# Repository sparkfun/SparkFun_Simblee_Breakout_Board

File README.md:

**NOTE:** *This product has been retired from our catalog. If you are looking for more up-to-date info, please check out some of these resources to see how other users are still hacking and improving on this product.*
* *[SparkFun Forum](https://forum.sparkfun.com/)*
* *[Comments Here on GitHub](https://github.com/sparkfun/SparkFun_Simblee_Breakout_Board/issues)*
* *[IRC Channel](https://www.sparkfun.com/news/263)*

SparkFun Simblee Breakout Board
==================

The [SparkFun Simblee Breakout Board](https://www.sparkfun.com/products/13632) is a programmable board that allows you to add mobile app functionality via Bluetooth Low Energy (BLE, or Bluetooth 4.0) to your embedded projects. Unlike other BLE solutions, the Simblee requires no specialized app development skills to realize the phone-side interface; all the necessary coding is done in the Arduino environment and then uploaded to a browser app on the phone.

[  
*SparkFun Simblee Breakout Board*](https://www.sparkfun.com/products/13632)

Design files and firmware files for the [SparkFun Simblee Breakout Board](https://www.sparkfun.com/products/13632).

Repository Contents
-------------------

* **/hardware** - Eagle PCB layout files
* **/Production** - Files to support SparkFun production

Documentation
--------------
* **[Simblee Concepts](https://learn.sparkfun.com/tutorials/simblee-concepts)** - Information about Simblee
* **[Hookup Guide](https://learn.sparkfun.com/tutorials/simblee-breakout-board-hookup-guide)** - Basic hookup guide

License Information
-------------------

All contents of this repository are released under [Creative Commons Share-alike 4.0](http://creativecommons.org/licenses/by-sa/4.0/).

Authors: Mike Hord @ SparkFun Electonics

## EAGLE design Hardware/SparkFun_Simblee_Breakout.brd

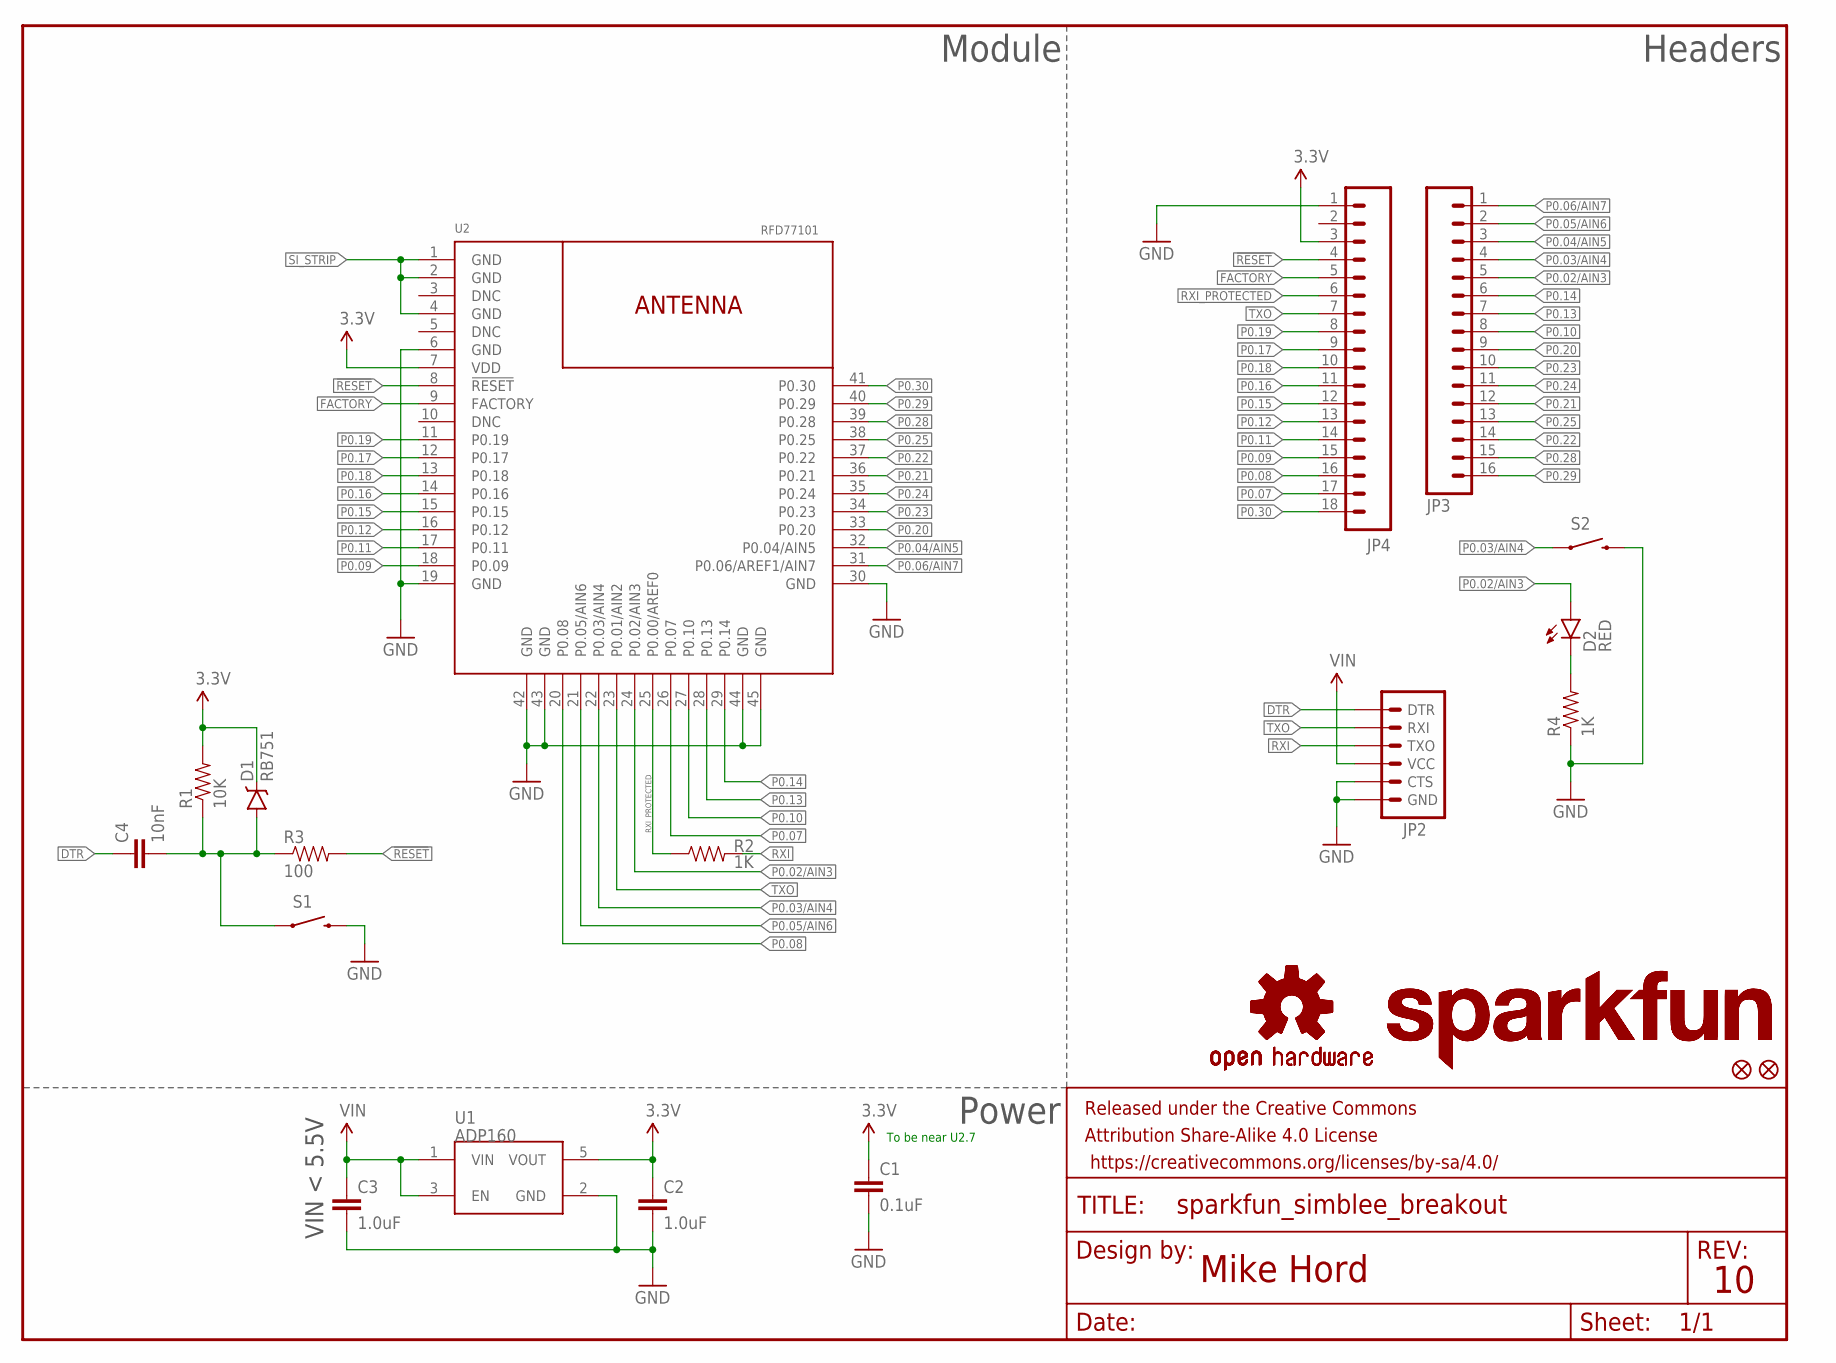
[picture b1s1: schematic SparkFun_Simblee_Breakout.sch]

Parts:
C1: 0.1uF; 0603-CAP
C2, C3: 1.0uF; 0603-CAP
C4: 10nF; 0603-CAP
D1: RB751; SOD-523
D2: RED; LED-0603
FID1, FID2: FIDUCIALUFIDUCIAL; MICRO-FIDUCIAL
FRAME1: FRAME-LETTER; CREATIVE_COMMONS
JP2: ARDUINO_SERIAL_PROGRAMPTH; 1X06
JP3: M16PTH; 1X16
JP4: M18_; 1X18
LOGO1, LOGO3: SFE_LOGO_NAME.1_INCH; SFE_LOGO_NAME_.1
LOGO2, LOGO4: OSHW-LOGOS; OSHW-LOGO-S
R1: 10K; 0603-RES
R2, R4: 1K; 0603-RES
R3: 100; 0603-RES
S1, S2: SWITCH-MOMENTARY-2SMD; TACTILE-SWITCH-SMD
U1: ADP160; SOT23-5
U2: RFD77101

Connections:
3.3V: C1.1, C2.1, D1.C, JP4.3, R1.2, U1.5 (VOUT), U2.7 (VDD)
!RESET: JP4.4, R3.2, U2.8 (!RESET!)
DTR: C4.1, JP2.1 (DTR)
FACTORY: JP4.5, U2.9 (FACTORY)
GND: C1.2, C2.2, C3.2, JP2.5 (CTS), JP2.6 (GND), JP4.1, R4.1, S1.3 (2), S2.3 (2), U1.2 (GND), U2.6 (GND), U2.19 (GND), U2.30 (GND), U2.42 (GND), U2.43 (GND), U2.44 (GND), U2.45 (GND)
unnamed: C4.2, D1.A, R1.1, R3.1, S1.1
unnamed: D2.C, R4.2
P0.02/AIN3: D2.A, JP3.5, U2.24 (P0.02/AIN3)
P0.03/AIN4: JP3.4, S2.1, U2.22 (P0.03/AIN4)
P0.04/AIN5: JP3.3, U2.32 (P0.04/AIN5)
P0.05/AIN6: JP3.2, U2.21 (P0.05/AIN6)
P0.06/AIN7: JP3.1, U2.31 (P0.06/AREF1/AIN7)
P0.07: JP4.17, U2.26 (P0.07)
P0.08: JP4.16, U2.20 (P0.08)
P0.09: JP4.15, U2.18 (P0.09)
P0.10: JP3.8, U2.27 (P0.10)
P0.11: JP4.14, U2.17 (P0.11)
P0.12: JP4.13, U2.16 (P0.12)
P0.13: JP3.7, U2.28 (P0.13)
P0.14: JP3.6, U2.29 (P0.14)
P0.15: JP4.12, U2.15 (P0.15)
P0.16: JP4.11, U2.14 (P0.16)
P0.17: JP4.9, U2.12 (P0.17)
P0.18: JP4.10, U2.13 (P0.18)
P0.19: JP4.8, U2.11 (P0.19)
P0.20: JP3.9, U2.33 (P0.20)
P0.21: JP3.12, U2.36 (P0.21)
P0.22: JP3.14, U2.37 (P0.22)
P0.23: JP3.10, U2.34 (P0.23)
P0.24: JP3.11, U2.35 (P0.24)
P0.25: JP3.13, U2.38 (P0.25)
P0.28: JP3.15, U2.39 (P0.28)
P0.29: JP3.16, U2.40 (P0.29)
P0.30: JP4.18, U2.41 (P0.30)
RXI: JP2.3 (TXO), R2.2
RXI_PROTECTED: JP4.6, R2.1, U2.25 (P0.00/AREF0)
SI_STRIP: U2.1 (GND), U2.2 (GND), U2.4 (GND)
TXO: JP2.2 (RXI), JP4.7, U2.23 (P0.01/AIN2)
VIN: C3.1, JP2.4 (VCC), U1.1 (VIN), U1.3 (EN)

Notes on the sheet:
Mike Hord
VIN < 5.5V
Module
Power
Headers
To be near U2.7

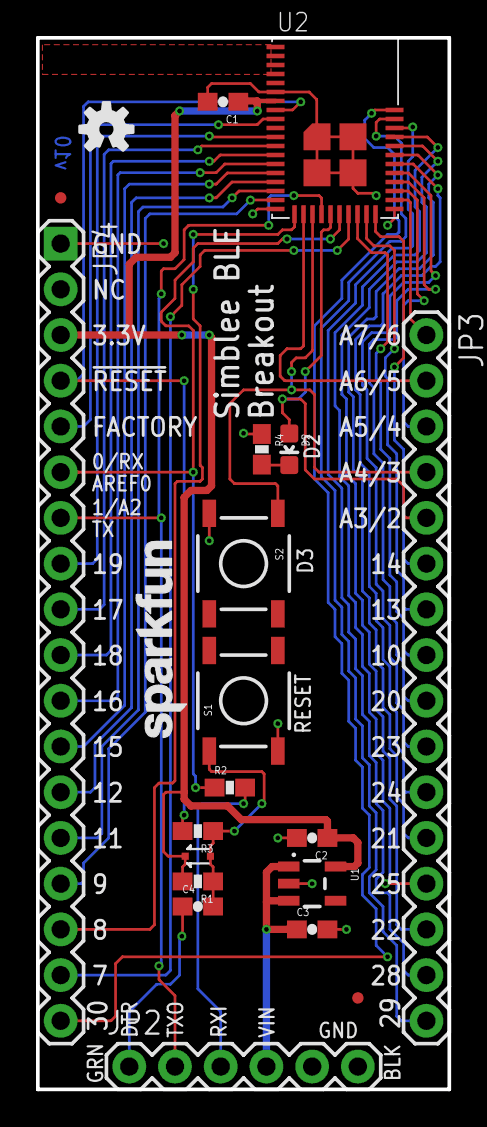
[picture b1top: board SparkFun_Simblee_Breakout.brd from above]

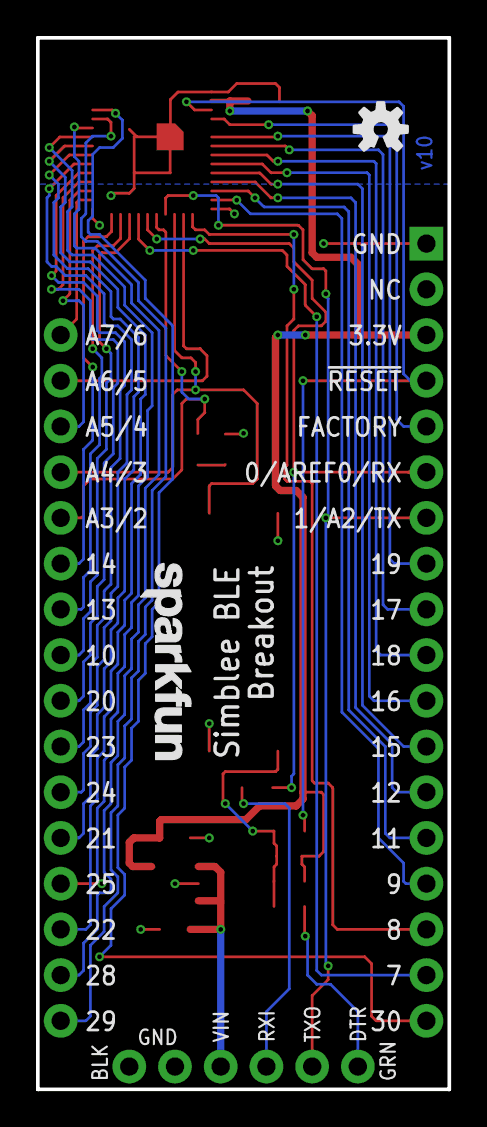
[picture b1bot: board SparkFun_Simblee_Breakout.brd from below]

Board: 2 copper layers, 22.9 x 58.4 mm, 24 parts (2 on the bottom side), 39 nets.

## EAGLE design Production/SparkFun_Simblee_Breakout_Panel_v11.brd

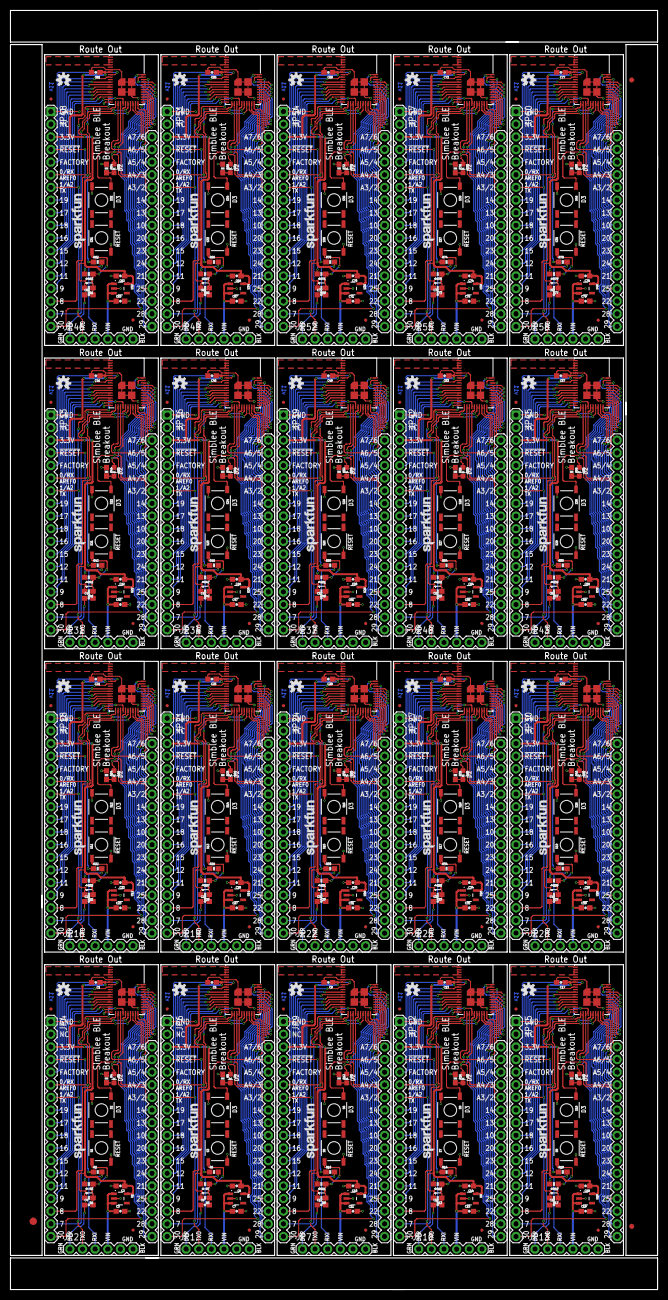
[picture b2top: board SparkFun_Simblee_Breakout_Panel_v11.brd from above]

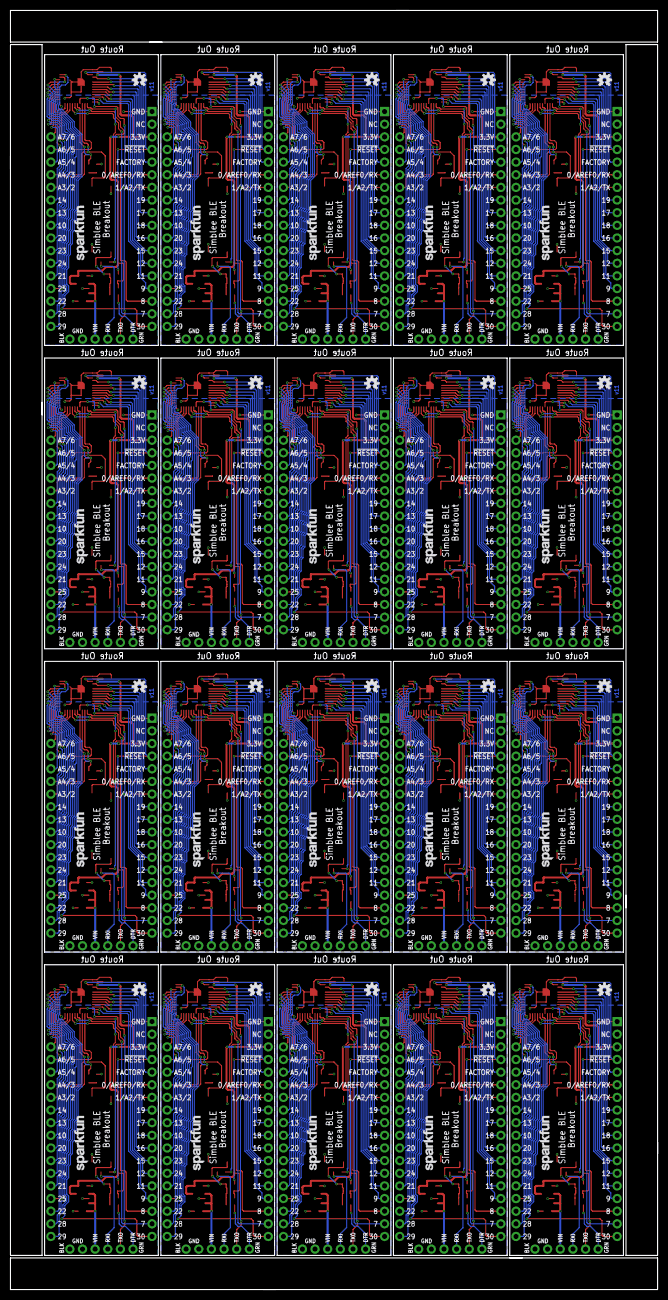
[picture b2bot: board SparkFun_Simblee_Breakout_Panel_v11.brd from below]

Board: 2 copper layers, 130.0 x 257.0 mm, 463 parts (40 on the bottom side), 780 nets.

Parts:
C1, C5, C9, C13, C17, C21, C25, C29, C33, C37, C41, C45, C49, C53, C57, C61, C65, C69, C73, C77: 0.1uF; 0603-CAP
C2, C3, C6, C7, C10, C11, C14, C15, C18, C19, C22, C23, C26, C27, C30, C31, C34, C35, C38, C39, C42, C43, C46, C47, C50, C51, C54, C55, C58, C59, C62, C63, C66, C67, C70, C71, C74, C75, C78, C79: 1.0uF; 0603-CAP
C4, C8, C12, C16, C20, C24, C28, C32, C36, C40, C44, C48, C52, C56, C60, C64, C68, C72, C76, C80: 10nF; 0603-CAP
D1, D3, D5, D7, D9, D11, D13, D15, D17, D19, D21, D23, D25, D27, D29, D31, D33, D35, D37, D39: RB751; SOD-523
D2, D4, D6, D8, D10, D12, D14, D16, D18, D20, D22, D24, D26, D28, D30, D32, D34, D36, D38, D40: RED; LED-0603
E$1: FIDUCIAL-1.5X3
E$5, E$6: FIDUCIAL-1X2
FID1, FID2, FID3, FID4, FID5, FID6, FID7, FID8, FID9, FID10, FID11, FID12, FID13, FID14, FID15, FID16, FID17, FID18, FID19, FID20, FID21, FID22, FID23, FID24, FID25, FID26, FID27, FID28, FID29, FID30, FID31, FID32, FID33, FID34, FID35, FID36, FID37, FID38, FID39, FID40: FIDUCIALUFIDUCIAL; MICRO-FIDUCIAL
JP1, JP2, JP7, JP10, JP13, JP16, JP19, JP22, JP25, JP28, JP31, JP34, JP37, JP40, JP43, JP46, JP49, JP52, JP55, JP58: 1X06
JP3, JP5, JP8, JP11, JP14, JP17, JP20, JP23, JP26, JP29, JP32, JP35, JP38, JP41, JP44, JP47, JP50, JP53, JP56, JP59: 1X16
JP4, JP6, JP9, JP12, JP15, JP18, JP21, JP24, JP27, JP30, JP33, JP36, JP39, JP42, JP45, JP48, JP51, JP54, JP57, JP60: 1X18
LOGO1, LOGO3, LOGO5, LOGO7, LOGO9, LOGO11, LOGO13, LOGO15, LOGO17, LOGO19, LOGO21, LOGO23, LOGO25, LOGO27, LOGO29, LOGO31, LOGO33, LOGO35, LOGO37, LOGO39, LOGO41, LOGO43, LOGO45, LOGO47, LOGO49, LOGO51, LOGO53, LOGO55, LOGO57, LOGO59, LOGO61, LOGO63, LOGO65, LOGO67, LOGO69, LOGO71, LOGO73, LOGO75, LOGO77, LOGO79: SFE_LOGO_NAME.1_INCH; SFE_LOGO_NAME_.1
LOGO2, LOGO4, LOGO6, LOGO8, LOGO10, LOGO12, LOGO14, LOGO16, LOGO18, LOGO20, LOGO22, LOGO24, LOGO26, LOGO28, LOGO30, LOGO32, LOGO34, LOGO36, LOGO38, LOGO40, LOGO42, LOGO44, LOGO46, LOGO48, LOGO50, LOGO52, LOGO54, LOGO56, LOGO58, LOGO60, LOGO62, LOGO64, LOGO66, LOGO68, LOGO70, LOGO72, LOGO74, LOGO76, LOGO78, LOGO80: OSHW-LOGOS; OSHW-LOGO-S
R1, R5, R9, R13, R17, R21, R25, R29, R33, R37, R41, R45, R49, R53, R57, R61, R65, R69, R73, R77: 10K; 0603-RES
R2, R4, R6, R8, R10, R12, R14, R16, R18, R20, R22, R24, R26, R28, R30, R32, R34, R36, R38, R40, R42, R44, R46, R48, R50, R52, R54, R56, R58, R60, R62, R64, R66, R68, R70, R72, R74, R76, R78, R80: 1K; 0603-RES
R3, R7, R11, R15, R19, R23, R27, R31, R35, R39, R43, R47, R51, R55, R59, R63, R67, R71, R75, R79: 100; 0603-RES
S1, S2, S3, S4, S5, S6, S7, S8, S9, S10, S11, S12, S13, S14, S15, S16, S17, S18, S19, S20, S21, S22, S23, S24, S25, S26, S27, S28, S29, S30, S31, S32, S33, S34, S35, S36, S37, S38, S39, S40: SWITCH-MOMENTARY-2SMD; TACTILE-SWITCH-SMD
U1, U4, U6, U8, U10, U12, U14, U16, U18, U20, U22, U24, U26, U28, U30, U32, U34, U36, U38, U40: ADP160; SOT23-5
U2, U3, U5, U7, U9, U11, U13, U15, U17, U19, U21, U23, U25, U27, U29, U31, U33, U35, U37, U39: RFD77101

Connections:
3.3V: C1.1, C2.1, D1.C, JP4.3, R1.2, U1.5, U2.7
3.3V1: C5.1, C6.1, D3.C, JP6.3, R5.2, U3.7, U4.5
3.3V2: C9.1, C10.1, D5.C, JP9.3, R9.2, U5.7, U6.5
3.3V3: C13.1, C14.1, D7.C, JP12.3, R13.2, U7.7, U8.5
3.3V4: C17.1, C18.1, D9.C, JP15.3, R17.2, U9.7, U10.5
3.3V5: C21.1, C22.1, D11.C, JP18.3, R21.2, U11.7, U12.5
3.3V6: C25.1, C26.1, D13.C, JP21.3, R25.2, U13.7, U14.5
3.3V7: C29.1, C30.1, D15.C, JP24.3, R29.2, U15.7, U16.5
3.3V8: C33.1, C34.1, D17.C, JP27.3, R33.2, U17.7, U18.5
3.3V9: C37.1, C38.1, D19.C, JP30.3, R37.2, U19.7, U20.5
3.3V10: C41.1, C42.1, D21.C, JP33.3, R41.2, U21.7, U22.5
3.3V11: C45.1, C46.1, D23.C, JP36.3, R45.2, U23.7, U24.5
3.3V12: C49.1, C50.1, D25.C, JP39.3, R49.2, U25.7, U26.5
3.3V13: C53.1, C54.1, D27.C, JP42.3, R53.2, U27.7, U28.5
3.3V14: C57.1, C58.1, D29.C, JP45.3, R57.2, U29.7, U30.5
3.3V15: C61.1, C62.1, D31.C, JP48.3, R61.2, U31.7, U32.5
3.3V16: C65.1, C66.1, D33.C, JP51.3, R65.2, U33.7, U34.5
3.3V17: C69.1, C70.1, D35.C, JP54.3, R69.2, U35.7, U36.5
3.3V18: C73.1, C74.1, D37.C, JP57.3, R73.2, U37.7, U38.5
3.3V19: C77.1, C78.1, D39.C, JP60.3, R77.2, U39.7, U40.5
!RESET: JP4.4, R3.2, U2.8
!RESET1: JP6.4, R7.2, U3.8
!RESET2: JP9.4, R11.2, U5.8
!RESET3: JP12.4, R15.2, U7.8
!RESET4: JP15.4, R19.2, U9.8
!RESET5: JP18.4, R23.2, U11.8
!RESET6: JP21.4, R27.2, U13.8
!RESET7: JP24.4, R31.2, U15.8
!RESET8: JP27.4, R35.2, U17.8
!RESET9: JP30.4, R39.2, U19.8
!RESET10: JP33.4, R43.2, U21.8
!RESET11: JP36.4, R47.2, U23.8
!RESET12: JP39.4, R51.2, U25.8
!RESET13: JP42.4, R55.2, U27.8
!RESET14: JP45.4, R59.2, U29.8
!RESET15: JP48.4, R63.2, U31.8
!RESET16: JP51.4, R67.2, U33.8
!RESET17: JP54.4, R71.2, U35.8
!RESET18: JP57.4, R75.2, U37.8
!RESET19: JP60.4, R79.2, U39.8
DTR: C4.1, JP2.1
DTR1: C8.1, JP1.1
DTR2: C12.1, JP7.1
DTR3: C16.1, JP10.1
DTR4: C20.1, JP13.1
DTR5: C24.1, JP16.1
DTR6: C28.1, JP19.1
DTR7: C32.1, JP22.1
DTR8: C36.1, JP25.1
DTR9: C40.1, JP28.1
DTR10: C44.1, JP31.1
DTR11: C48.1, JP34.1
DTR12: C52.1, JP37.1
DTR13: C56.1, JP40.1
DTR14: C60.1, JP43.1
DTR15: C64.1, JP46.1
DTR16: C68.1, JP49.1
DTR17: C72.1, JP52.1
DTR18: C76.1, JP55.1
DTR19: C80.1, JP58.1
FACTORY: JP4.5, U2.9
FACTORY1: JP6.5, U3.9
FACTORY2: JP9.5, U5.9
FACTORY3: JP12.5, U7.9
FACTORY4: JP15.5, U9.9
FACTORY5: JP18.5, U11.9
FACTORY6: JP21.5, U13.9
FACTORY7: JP24.5, U15.9
FACTORY8: JP27.5, U17.9
FACTORY9: JP30.5, U19.9
FACTORY10: JP33.5, U21.9
FACTORY11: JP36.5, U23.9
FACTORY12: JP39.5, U25.9
FACTORY13: JP42.5, U27.9
FACTORY14: JP45.5, U29.9
FACTORY15: JP48.5, U31.9
FACTORY16: JP51.5, U33.9
FACTORY17: JP54.5, U35.9
FACTORY18: JP57.5, U37.9
FACTORY19: JP60.5, U39.9
GND: C1.2, C2.2, C3.2, JP2.5, JP2.6, JP4.1, R4.1, S1.3, S2.3, U1.2, U2.6, U2.19, U2.30, U2.42, U2.43, U2.44, U2.45
GND1: C5.2, C6.2, C7.2, JP1.5, JP1.6, JP6.1, R8.1, S3.3, S4.3, U3.6, U3.19, U3.30, U3.42, U3.43, U3.44, U3.45, U4.2
GND2: C9.2, C10.2, C11.2, JP7.5, JP7.6, JP9.1, R12.1, S5.3, S6.3, U5.6, U5.19, U5.30, U5.42, U5.43, U5.44, U5.45, U6.2
GND3: C13.2, C14.2, C15.2, JP10.5, JP10.6, JP12.1, R16.1, S7.3, S8.3, U7.6, U7.19, U7.30, U7.42, U7.43, U7.44, U7.45, U8.2
GND4: C17.2, C18.2, C19.2, JP13.5, JP13.6, JP15.1, R20.1, S9.3, S10.3, U9.6, U9.19, U9.30, U9.42, U9.43, U9.44, U9.45, U10.2
GND5: C21.2, C22.2, C23.2, JP16.5, JP16.6, JP18.1, R24.1, S11.3, S12.3, U11.6, U11.19, U11.30, U11.42, U11.43, U11.44, U11.45, U12.2
GND6: C25.2, C26.2, C27.2, JP19.5, JP19.6, JP21.1, R28.1, S13.3, S14.3, U13.6, U13.19, U13.30, U13.42, U13.43, U13.44, U13.45, U14.2
GND7: C29.2, C30.2, C31.2, JP22.5, JP22.6, JP24.1, R32.1, S15.3, S16.3, U15.6, U15.19, U15.30, U15.42, U15.43, U15.44, U15.45, U16.2
GND8: C33.2, C34.2, C35.2, JP25.5, JP25.6, JP27.1, R36.1, S17.3, S18.3, U17.6, U17.19, U17.30, U17.42, U17.43, U17.44, U17.45, U18.2
GND9: C37.2, C38.2, C39.2, JP28.5, JP28.6, JP30.1, R40.1, S19.3, S20.3, U19.6, U19.19, U19.30, U19.42, U19.43, U19.44, U19.45, U20.2
GND10: C41.2, C42.2, C43.2, JP31.5, JP31.6, JP33.1, R44.1, S21.3, S22.3, U21.6, U21.19, U21.30, U21.42, U21.43, U21.44, U21.45, U22.2
GND11: C45.2, C46.2, C47.2, JP34.5, JP34.6, JP36.1, R48.1, S23.3, S24.3, U23.6, U23.19, U23.30, U23.42, U23.43, U23.44, U23.45, U24.2
GND12: C49.2, C50.2, C51.2, JP37.5, JP37.6, JP39.1, R52.1, S25.3, S26.3, U25.6, U25.19, U25.30, U25.42, U25.43, U25.44, U25.45, U26.2
GND13: C53.2, C54.2, C55.2, JP40.5, JP40.6, JP42.1, R56.1, S27.3, S28.3, U27.6, U27.19, U27.30, U27.42, U27.43, U27.44, U27.45, U28.2
GND14: C57.2, C58.2, C59.2, JP43.5, JP43.6, JP45.1, R60.1, S29.3, S30.3, U29.6, U29.19, U29.30, U29.42, U29.43, U29.44, U29.45, U30.2
GND15: C61.2, C62.2, C63.2, JP46.5, JP46.6, JP48.1, R64.1, S31.3, S32.3, U31.6, U31.19, U31.30, U31.42, U31.43, U31.44, U31.45, U32.2
GND16: C65.2, C66.2, C67.2, JP49.5, JP49.6, JP51.1, R68.1, S33.3, S34.3, U33.6, U33.19, U33.30, U33.42, U33.43, U33.44, U33.45, U34.2
GND17: C69.2, C70.2, C71.2, JP52.5, JP52.6, JP54.1, R72.1, S35.3, S36.3, U35.6, U35.19, U35.30, U35.42, U35.43, U35.44, U35.45, U36.2
GND18: C73.2, C74.2, C75.2, JP55.5, JP55.6, JP57.1, R76.1, S37.3, S38.3, U37.6, U37.19, U37.30, U37.42, U37.43, U37.44, U37.45, U38.2
GND19: C77.2, C78.2, C79.2, JP58.5, JP58.6, JP60.1, R80.1, S39.3, S40.3, U39.6, U39.19, U39.30, U39.42, U39.43, U39.44, U39.45, U40.2
unnamed: C4.2, D1.A, R1.1, R3.1, S1.1
unnamed: D2.C, R4.2
unnamed: C8.2, D3.A, R5.1, R7.1, S3.1
unnamed: D4.C, R8.2
unnamed: C12.2, D5.A, R9.1, R11.1, S5.1
unnamed: D6.C, R12.2
unnamed: C16.2, D7.A, R13.1, R15.1, S7.1
unnamed: D8.C, R16.2
unnamed: C20.2, D9.A, R17.1, R19.1, S9.1
unnamed: D10.C, R20.2
unnamed: C24.2, D11.A, R21.1, R23.1, S11.1
unnamed: D12.C, R24.2
unnamed: C28.2, D13.A, R25.1, R27.1, S13.1
unnamed: D14.C, R28.2
unnamed: C32.2, D15.A, R29.1, R31.1, S15.1
unnamed: D16.C, R32.2
unnamed: C36.2, D17.A, R33.1, R35.1, S17.1
unnamed: D18.C, R36.2
unnamed: C40.2, D19.A, R37.1, R39.1, S19.1
unnamed: D20.C, R40.2
unnamed: C44.2, D21.A, R41.1, R43.1, S21.1
unnamed: D22.C, R44.2
unnamed: C48.2, D23.A, R45.1, R47.1, S23.1
unnamed: D24.C, R48.2
unnamed: C52.2, D25.A, R49.1, R51.1, S25.1
unnamed: D26.C, R52.2
unnamed: C56.2, D27.A, R53.1, R55.1, S27.1
unnamed: D28.C, R56.2
unnamed: C60.2, D29.A, R57.1, R59.1, S29.1
unnamed: D30.C, R60.2
unnamed: C64.2, D31.A, R61.1, R63.1, S31.1
unnamed: D32.C, R64.2
unnamed: C68.2, D33.A, R65.1, R67.1, S33.1
unnamed: D34.C, R68.2
unnamed: C72.2, D35.A, R69.1, R71.1, S35.1
unnamed: D36.C, R72.2
unnamed: C76.2, D37.A, R73.1, R75.1, S37.1
unnamed: D38.C, R76.2
unnamed: C80.2, D39.A, R77.1, R79.1, S39.1
unnamed: D40.C, R80.2
P0.01: JP5.6, U3.29
P0.02: JP5.7, U3.28
P0.02/AIN1: D4.A, JP5.5, U3.24
P0.02/AIN2: D6.A, JP8.5, U5.24
P0.02/AIN3: D2.A, JP3.5, U2.24
P0.02/AIN4: D8.A, JP11.5, U7.24
P0.02/AIN5: D10.A, JP14.5, U9.24
P0.02/AIN6: D12.A, JP17.5, U11.24
P0.02/AIN7: D14.A, JP20.5, U13.24
P0.02/AIN8: D16.A, JP23.5, U15.24
P0.02/AIN9: D18.A, JP26.5, U17.24
P0.02/AIN10: D20.A, JP29.5, U19.24
P0.02/AIN11: D22.A, JP32.5, U21.24
P0.02/AIN12: D24.A, JP35.5, U23.24
P0.02/AIN13: D26.A, JP38.5, U25.24
P0.02/AIN14: D28.A, JP41.5, U27.24
P0.02/AIN15: D30.A, JP44.5, U29.24
P0.02/AIN16: D32.A, JP47.5, U31.24
P0.02/AIN17: D34.A, JP50.5, U33.24
P0.02/AIN18: D36.A, JP53.5, U35.24
P0.02/AIN19: D38.A, JP56.5, U37.24
P0.02/AIN20: D40.A, JP59.5, U39.24
P0.03: JP5.8, U3.27
P0.03/AIN1: JP5.4, S4.1, U3.22
P0.03/AIN2: JP8.4, S6.1, U5.22
P0.03/AIN3: JP11.4, S8.1, U7.22
P0.03/AIN4: JP3.4, S2.1, U2.22
P0.03/AIN5: JP14.4, S10.1, U9.22
P0.03/AIN6: JP17.4, S12.1, U11.22
P0.03/AIN7: JP20.4, S14.1, U13.22
P0.03/AIN8: JP23.4, S16.1, U15.22
P0.03/AIN9: JP26.4, S18.1, U17.22
P0.03/AIN10: JP29.4, S20.1, U19.22
P0.03/AIN11: JP32.4, S22.1, U21.22
P0.03/AIN12: JP35.4, S24.1, U23.22
P0.03/AIN13: JP38.4, S26.1, U25.22
P0.03/AIN14: JP41.4, S28.1, U27.22
P0.03/AIN15: JP44.4, S30.1, U29.22
P0.03/AIN16: JP47.4, S32.1, U31.22
P0.03/AIN17: JP50.4, S34.1, U33.22
P0.03/AIN18: JP53.4, S36.1, U35.22
P0.03/AIN19: JP56.4, S38.1, U37.22
P0.03/AIN20: JP59.4, S40.1, U39.22
P0.04: JP6.17, U3.26
P0.04/AIN1: JP5.3, U3.32
P0.04/AIN2: JP8.3, U5.32
P0.04/AIN3: JP11.3, U7.32
P0.04/AIN4: JP14.3, U9.32
P0.04/AIN5: JP3.3, U2.32
P0.04/AIN6: JP17.3, U11.32
P0.04/AIN7: JP20.3, U13.32
P0.04/AIN8: JP23.3, U15.32
P0.04/AIN9: JP26.3, U17.32
P0.04/AIN10: JP29.3, U19.32
P0.04/AIN11: JP32.3, U21.32
P0.04/AIN12: JP35.3, U23.32
P0.04/AIN13: JP38.3, U25.32
P0.04/AIN14: JP41.3, U27.32
P0.04/AIN15: JP44.3, U29.32
P0.04/AIN16: JP47.3, U31.32
P0.04/AIN17: JP50.3, U33.32
P0.04/AIN18: JP53.3, U35.32
P0.04/AIN19: JP56.3, U37.32
P0.04/AIN20: JP59.3, U39.32
P0.05: JP6.16, U3.20
P0.05/AIN1: JP5.2, U3.21
P0.05/AIN2: JP8.2, U5.21
P0.05/AIN3: JP11.2, U7.21
P0.05/AIN4: JP14.2, U9.21
P0.05/AIN5: JP17.2, U11.21
P0.05/AIN6: JP3.2, U2.21
P0.05/AIN7: JP20.2, U13.21
P0.05/AIN8: JP23.2, U15.21
P0.05/AIN9: JP26.2, U17.21
P0.05/AIN10: JP29.2, U19.21
P0.05/AIN11: JP32.2, U21.21
P0.05/AIN12: JP35.2, U23.21
P0.05/AIN13: JP38.2, U25.21
P0.05/AIN14: JP41.2, U27.21
P0.05/AIN15: JP44.2, U29.21
P0.05/AIN16: JP47.2, U31.21
P0.05/AIN17: JP50.2, U33.21
P0.05/AIN18: JP53.2, U35.21
P0.05/AIN19: JP56.2, U37.21
P0.05/AIN20: JP59.2, U39.21
P0.06: JP6.18, U3.41
P0.06/AIN1: JP5.1, U3.31
P0.06/AIN2: JP8.1, U5.31
P0.06/AIN3: JP11.1, U7.31
P0.06/AIN4: JP14.1, U9.31
P0.06/AIN5: JP17.1, U11.31
P0.06/AIN6: JP20.1, U13.31
P0.06/AIN7: JP3.1, U2.31
P0.06/AIN8: JP23.1, U15.31
P0.06/AIN9: JP26.1, U17.31
P0.06/AIN10: JP29.1, U19.31
P0.06/AIN11: JP32.1, U21.31
P0.06/AIN12: JP35.1, U23.31
P0.06/AIN13: JP38.1, U25.31
P0.06/AIN14: JP41.1, U27.31
P0.06/AIN15: JP44.1, U29.31
P0.06/AIN16: JP47.1, U31.31
P0.06/AIN17: JP50.1, U33.31
P0.06/AIN18: JP53.1, U35.31
P0.06/AIN19: JP56.1, U37.31
P0.06/AIN20: JP59.1, U39.31
P0.07: JP4.17, U2.26
P0.08: JP4.16, U2.20
P0.09: JP4.15, U2.18
P0.10: JP3.8, U2.27
P0.11: JP4.14, U2.17
P0.12: JP4.13, U2.16
P0.13: JP3.7, U2.28
P0.14: JP3.6, U2.29
P0.15: JP4.12, U2.15
P0.16: JP4.11, U2.14
P0.17: JP4.9, U2.12
P0.18: JP4.10, U2.13
P0.19: JP4.8, U2.11
P0.20: JP3.9, U2.33
P0.21: JP3.12, U2.36
P0.22: JP3.14, U2.37
P0.23: JP3.10, U2.34
P0.24: JP3.11, U2.35
P0.25: JP3.13, U2.38
P0.26: JP5.16, U3.40
P0.27: JP5.15, U3.39
P0.28: JP3.15, U2.39
P0.29: JP3.16, U2.40
P0.30: JP4.18, U2.41
P0.31: JP5.13, U3.38
P0.32: JP5.14, U3.37
P0.33: JP5.12, U3.36
P0.34: JP5.11, U3.35
P0.35: JP5.10, U3.34
P0.36: JP5.9, U3.33
P0.37: JP6.15, U3.18
P0.38: JP6.14, U3.17
P0.39: JP6.13, U3.16
P0.40: JP6.12, U3.15
P0.41: JP6.11, U3.14
P0.42: JP6.10, U3.13
P0.43: JP6.9, U3.12
P0.44: JP6.8, U3.11
P0.45: JP8.6, U5.29
P0.46: JP8.7, U5.28
P0.47: JP8.8, U5.27
P0.48: JP9.17, U5.26
P0.49: JP9.16, U5.20
P0.50: JP9.18, U5.41
P0.51: JP8.16, U5.40
P0.52: JP8.15, U5.39
P0.53: JP8.13, U5.38
P0.54: JP8.14, U5.37
P0.55: JP8.12, U5.36
P0.56: JP8.11, U5.35
P0.57: JP8.10, U5.34
P0.58: JP8.9, U5.33
P0.59: JP9.15, U5.18
P0.60: JP9.14, U5.17
P0.61: JP9.13, U5.16
P0.62: JP9.12, U5.15
P0.63: JP9.11, U5.14
P0.64: JP9.10, U5.13
P0.65: JP9.9, U5.12
P0.66: JP9.8, U5.11
P0.67: JP11.6, U7.29
P0.68: JP11.7, U7.28
P0.69: JP11.8, U7.27
P0.70: JP12.17, U7.26
P0.71: JP12.16, U7.20
P0.72: JP12.18, U7.41
P0.73: JP11.16, U7.40
P0.74: JP11.15, U7.39
P0.75: JP11.13, U7.38
P0.76: JP11.14, U7.37
P0.77: JP11.12, U7.36
P0.78: JP11.11, U7.35
P0.79: JP11.10, U7.34
P0.80: JP11.9, U7.33
P0.81: JP12.15, U7.18
P0.82: JP12.14, U7.17
P0.83: JP12.13, U7.16
P0.84: JP12.12, U7.15
P0.85: JP12.11, U7.14
P0.86: JP12.10, U7.13
P0.87: JP12.9, U7.12
P0.88: JP12.8, U7.11
P0.89: JP14.6, U9.29
P0.90: JP14.7, U9.28
P0.91: JP14.8, U9.27
P0.92: JP15.17, U9.26
P0.93: JP15.16, U9.20
P0.94: JP15.18, U9.41
P0.95: JP14.16, U9.40
P0.96: JP14.15, U9.39
P0.97: JP14.13, U9.38
P0.98: JP14.14, U9.37
P0.99: JP14.12, U9.36
P0.100: JP14.11, U9.35
P0.101: JP14.10, U9.34
P0.102: JP14.9, U9.33
P0.103: JP15.15, U9.18
P0.104: JP15.14, U9.17
P0.105: JP15.13, U9.16
P0.106: JP15.12, U9.15
P0.107: JP15.11, U9.14
P0.108: JP15.10, U9.13
P0.109: JP15.9, U9.12
P0.110: JP15.8, U9.11
P0.111: JP17.6, U11.29
P0.112: JP17.7, U11.28
P0.113: JP17.8, U11.27
P0.114: JP18.17, U11.26
P0.115: JP18.16, U11.20
P0.116: JP18.18, U11.41
P0.117: JP17.16, U11.40
P0.118: JP17.15, U11.39
P0.119: JP17.13, U11.38
P0.120: JP17.14, U11.37
P0.121: JP17.12, U11.36
P0.122: JP17.11, U11.35
P0.123: JP17.10, U11.34
P0.124: JP17.9, U11.33
P0.125: JP18.15, U11.18
P0.126: JP18.14, U11.17
P0.127: JP18.13, U11.16
P0.128: JP18.12, U11.15
P0.129: JP18.11, U11.14
P0.130: JP18.10, U11.13
P0.131: JP18.9, U11.12
P0.132: JP18.8, U11.11
P0.133: JP20.6, U13.29
P0.134: JP20.7, U13.28
P0.135: JP20.8, U13.27
P0.136: JP21.17, U13.26
P0.137: JP21.16, U13.20
P0.138: JP21.18, U13.41
P0.139: JP20.16, U13.40
P0.140: JP20.15, U13.39
P0.141: JP20.13, U13.38
P0.142: JP20.14, U13.37
P0.143: JP20.12, U13.36
P0.144: JP20.11, U13.35
P0.145: JP20.10, U13.34
P0.146: JP20.9, U13.33
P0.147: JP21.15, U13.18
P0.148: JP21.14, U13.17
P0.149: JP21.13, U13.16
P0.150: JP21.12, U13.15
P0.151: JP21.11, U13.14
P0.152: JP21.10, U13.13
P0.153: JP21.9, U13.12
P0.154: JP21.8, U13.11
P0.155: JP23.6, U15.29
P0.156: JP23.7, U15.28
P0.157: JP23.8, U15.27
P0.158: JP24.17, U15.26
P0.159: JP24.16, U15.20
P0.160: JP24.18, U15.41
P0.161: JP23.16, U15.40
P0.162: JP23.15, U15.39
P0.163: JP23.13, U15.38
P0.164: JP23.14, U15.37
P0.165: JP23.12, U15.36
P0.166: JP23.11, U15.35
P0.167: JP23.10, U15.34
P0.168: JP23.9, U15.33
P0.169: JP24.15, U15.18
P0.170: JP24.14, U15.17
P0.171: JP24.13, U15.16
P0.172: JP24.12, U15.15
P0.173: JP24.11, U15.14
P0.174: JP24.10, U15.13
P0.175: JP24.9, U15.12
P0.176: JP24.8, U15.11
P0.177: JP26.6, U17.29
P0.178: JP26.7, U17.28
P0.179: JP26.8, U17.27
P0.180: JP27.17, U17.26
P0.181: JP27.16, U17.20
P0.182: JP27.18, U17.41
P0.183: JP26.16, U17.40
P0.184: JP26.15, U17.39
P0.185: JP26.13, U17.38
P0.186: JP26.14, U17.37
P0.187: JP26.12, U17.36
P0.188: JP26.11, U17.35
P0.189: JP26.10, U17.34
P0.190: JP26.9, U17.33
P0.191: JP27.15, U17.18
P0.192: JP27.14, U17.17
P0.193: JP27.13, U17.16
P0.194: JP27.12, U17.15
P0.195: JP27.11, U17.14
P0.196: JP27.10, U17.13
P0.197: JP27.9, U17.12
P0.198: JP27.8, U17.11
P0.199: JP29.6, U19.29
P0.200: JP29.7, U19.28
P0.201: JP29.8, U19.27
P0.202: JP30.17, U19.26
P0.203: JP30.16, U19.20
P0.204: JP30.18, U19.41
P0.205: JP29.16, U19.40
P0.206: JP29.15, U19.39
P0.207: JP29.13, U19.38
P0.208: JP29.14, U19.37
P0.209: JP29.12, U19.36
P0.210: JP29.11, U19.35
P0.211: JP29.10, U19.34
P0.212: JP29.9, U19.33
P0.213: JP30.15, U19.18
P0.214: JP30.14, U19.17
P0.215: JP30.13, U19.16
P0.216: JP30.12, U19.15
P0.217: JP30.11, U19.14
P0.218: JP30.10, U19.13
P0.219: JP30.9, U19.12
P0.220: JP30.8, U19.11
P0.221: JP32.6, U21.29
P0.222: JP32.7, U21.28
P0.223: JP32.8, U21.27
P0.224: JP33.17, U21.26
P0.225: JP33.16, U21.20
P0.226: JP33.18, U21.41
P0.227: JP32.16, U21.40
P0.228: JP32.15, U21.39
P0.229: JP32.13, U21.38
P0.230: JP32.14, U21.37
P0.231: JP32.12, U21.36
P0.232: JP32.11, U21.35
P0.233: JP32.10, U21.34
P0.234: JP32.9, U21.33
P0.235: JP33.15, U21.18
P0.236: JP33.14, U21.17
P0.237: JP33.13, U21.16
P0.238: JP33.12, U21.15
P0.239: JP33.11, U21.14
P0.240: JP33.10, U21.13
P0.241: JP33.9, U21.12
P0.242: JP33.8, U21.11
P0.243: JP35.6, U23.29
P0.244: JP35.7, U23.28
P0.245: JP35.8, U23.27
P0.246: JP36.17, U23.26
P0.247: JP36.16, U23.20
P0.248: JP36.18, U23.41
P0.249: JP35.16, U23.40
P0.250: JP35.15, U23.39
P0.251: JP35.13, U23.38
P0.252: JP35.14, U23.37
P0.253: JP35.12, U23.36
P0.254: JP35.11, U23.35
P0.255: JP35.10, U23.34
P0.256: JP35.9, U23.33
P0.257: JP36.15, U23.18
P0.258: JP36.14, U23.17
P0.259: JP36.13, U23.16
P0.260: JP36.12, U23.15
P0.261: JP36.11, U23.14
P0.262: JP36.10, U23.13
P0.263: JP36.9, U23.12
P0.264: JP36.8, U23.11
P0.265: JP38.6, U25.29
P0.266: JP38.7, U25.28
P0.267: JP38.8, U25.27
P0.268: JP39.17, U25.26
P0.269: JP39.16, U25.20
P0.270: JP39.18, U25.41
P0.271: JP38.16, U25.40
P0.272: JP38.15, U25.39
P0.273: JP38.13, U25.38
P0.274: JP38.14, U25.37
P0.275: JP38.12, U25.36
P0.276: JP38.11, U25.35
P0.277: JP38.10, U25.34
P0.278: JP38.9, U25.33
P0.279: JP39.15, U25.18
P0.280: JP39.14, U25.17
P0.281: JP39.13, U25.16
P0.282: JP39.12, U25.15
P0.283: JP39.11, U25.14
P0.284: JP39.10, U25.13
P0.285: JP39.9, U25.12
P0.286: JP39.8, U25.11
P0.287: JP41.6, U27.29
P0.288: JP41.7, U27.28
P0.289: JP41.8, U27.27
P0.290: JP42.17, U27.26
P0.291: JP42.16, U27.20
P0.292: JP42.18, U27.41
P0.293: JP41.16, U27.40
P0.294: JP41.15, U27.39
P0.295: JP41.13, U27.38
P0.296: JP41.14, U27.37
P0.297: JP41.12, U27.36
P0.298: JP41.11, U27.35
P0.299: JP41.10, U27.34
P0.300: JP41.9, U27.33
P0.301: JP42.15, U27.18
P0.302: JP42.14, U27.17
P0.303: JP42.13, U27.16
P0.304: JP42.12, U27.15
P0.305: JP42.11, U27.14
P0.306: JP42.10, U27.13
P0.307: JP42.9, U27.12
P0.308: JP42.8, U27.11
P0.309: JP44.6, U29.29
P0.310: JP44.7, U29.28
P0.311: JP44.8, U29.27
P0.312: JP45.17, U29.26
P0.313: JP45.16, U29.20
P0.314: JP45.18, U29.41
P0.315: JP44.16, U29.40
P0.316: JP44.15, U29.39
P0.317: JP44.13, U29.38
P0.318: JP44.14, U29.37
P0.319: JP44.12, U29.36
P0.320: JP44.11, U29.35
P0.321: JP44.10, U29.34
P0.322: JP44.9, U29.33
P0.323: JP45.15, U29.18
P0.324: JP45.14, U29.17
P0.325: JP45.13, U29.16
P0.326: JP45.12, U29.15
P0.327: JP45.11, U29.14
P0.328: JP45.10, U29.13
P0.329: JP45.9, U29.12
P0.330: JP45.8, U29.11
P0.331: JP47.6, U31.29
P0.332: JP47.7, U31.28
P0.333: JP47.8, U31.27
P0.334: JP48.17, U31.26
P0.335: JP48.16, U31.20
P0.336: JP48.18, U31.41
P0.337: JP47.16, U31.40
P0.338: JP47.15, U31.39
P0.339: JP47.13, U31.38
P0.340: JP47.14, U31.37
P0.341: JP47.12, U31.36
P0.342: JP47.11, U31.35
P0.343: JP47.10, U31.34
P0.344: JP47.9, U31.33
P0.345: JP48.15, U31.18
P0.346: JP48.14, U31.17
P0.347: JP48.13, U31.16
P0.348: JP48.12, U31.15
P0.349: JP48.11, U31.14
P0.350: JP48.10, U31.13
P0.351: JP48.9, U31.12
P0.352: JP48.8, U31.11
P0.353: JP50.6, U33.29
P0.354: JP50.7, U33.28
P0.355: JP50.8, U33.27
P0.356: JP51.17, U33.26
P0.357: JP51.16, U33.20
P0.358: JP51.18, U33.41
P0.359: JP50.16, U33.40
P0.360: JP50.15, U33.39
P0.361: JP50.13, U33.38
P0.362: JP50.14, U33.37
P0.363: JP50.12, U33.36
P0.364: JP50.11, U33.35
P0.365: JP50.10, U33.34
P0.366: JP50.9, U33.33
P0.367: JP51.15, U33.18
P0.368: JP51.14, U33.17
P0.369: JP51.13, U33.16
P0.370: JP51.12, U33.15
P0.371: JP51.11, U33.14
P0.372: JP51.10, U33.13
P0.373: JP51.9, U33.12
P0.374: JP51.8, U33.11
P0.375: JP53.6, U35.29
P0.376: JP53.7, U35.28
P0.377: JP53.8, U35.27
P0.378: JP54.17, U35.26
P0.379: JP54.16, U35.20
P0.380: JP54.18, U35.41
P0.381: JP53.16, U35.40
P0.382: JP53.15, U35.39
P0.383: JP53.13, U35.38
P0.384: JP53.14, U35.37
P0.385: JP53.12, U35.36
P0.386: JP53.11, U35.35
P0.387: JP53.10, U35.34
P0.388: JP53.9, U35.33
P0.389: JP54.15, U35.18
P0.390: JP54.14, U35.17
P0.391: JP54.13, U35.16
P0.392: JP54.12, U35.15
P0.393: JP54.11, U35.14
P0.394: JP54.10, U35.13
P0.395: JP54.9, U35.12
P0.396: JP54.8, U35.11
P0.397: JP56.6, U37.29
P0.398: JP56.7, U37.28
P0.399: JP56.8, U37.27
P0.400: JP57.17, U37.26
P0.401: JP57.16, U37.20
P0.402: JP57.18, U37.41
P0.403: JP56.16, U37.40
P0.404: JP56.15, U37.39
P0.405: JP56.13, U37.38
P0.406: JP56.14, U37.37
P0.407: JP56.12, U37.36
P0.408: JP56.11, U37.35
P0.409: JP56.10, U37.34
P0.410: JP56.9, U37.33
P0.411: JP57.15, U37.18
P0.412: JP57.14, U37.17
P0.413: JP57.13, U37.16
P0.414: JP57.12, U37.15
P0.415: JP57.11, U37.14
P0.416: JP57.10, U37.13
P0.417: JP57.9, U37.12
P0.418: JP57.8, U37.11
P0.419: JP59.6, U39.29
P0.420: JP59.7, U39.28
P0.421: JP59.8, U39.27
P0.422: JP60.17, U39.26
P0.423: JP60.16, U39.20
P0.424: JP60.18, U39.41
P0.425: JP59.16, U39.40
P0.426: JP59.15, U39.39
P0.427: JP59.13, U39.38
P0.428: JP59.14, U39.37
P0.429: JP59.12, U39.36
P0.430: JP59.11, U39.35
P0.431: JP59.10, U39.34
P0.432: JP59.9, U39.33
P0.433: JP60.15, U39.18
P0.434: JP60.14, U39.17
P0.435: JP60.13, U39.16
P0.436: JP60.12, U39.15
P0.437: JP60.11, U39.14
P0.438: JP60.10, U39.13
P0.439: JP60.9, U39.12
P0.440: JP60.8, U39.11
RXI: JP2.3, R2.2
RXI1: JP1.3, R6.2
RXI2: JP7.3, R10.2
RXI3: JP10.3, R14.2
RXI4: JP13.3, R18.2
RXI5: JP16.3, R22.2
RXI6: JP19.3, R26.2
RXI7: JP22.3, R30.2
RXI8: JP25.3, R34.2
RXI9: JP28.3, R38.2
RXI10: JP31.3, R42.2
RXI11: JP34.3, R46.2
RXI12: JP37.3, R50.2
RXI13: JP40.3, R54.2
RXI14: JP43.3, R58.2
RXI15: JP46.3, R62.2
RXI16: JP49.3, R66.2
RXI17: JP52.3, R70.2
RXI18: JP55.3, R74.2
RXI19: JP58.3, R78.2
RXI_PROTECTED: JP4.6, R2.1, U2.25
RXI_PROTECTED1: JP6.6, R6.1, U3.25
RXI_PROTECTED2: JP9.6, R10.1, U5.25
RXI_PROTECTED3: JP12.6, R14.1, U7.25
RXI_PROTECTED4: JP15.6, R18.1, U9.25
RXI_PROTECTED5: JP18.6, R22.1, U11.25
RXI_PROTECTED6: JP21.6, R26.1, U13.25
RXI_PROTECTED7: JP24.6, R30.1, U15.25
RXI_PROTECTED8: JP27.6, R34.1, U17.25
RXI_PROTECTED9: JP30.6, R38.1, U19.25
RXI_PROTECTED10: JP33.6, R42.1, U21.25
RXI_PROTECTED11: JP36.6, R46.1, U23.25
RXI_PROTECTED12: JP39.6, R50.1, U25.25
RXI_PROTECTED13: JP42.6, R54.1, U27.25
RXI_PROTECTED14: JP45.6, R58.1, U29.25
RXI_PROTECTED15: JP48.6, R62.1, U31.25
RXI_PROTECTED16: JP51.6, R66.1, U33.25
RXI_PROTECTED17: JP54.6, R70.1, U35.25
RXI_PROTECTED18: JP57.6, R74.1, U37.25
RXI_PROTECTED19: JP60.6, R78.1, U39.25
SI_STRIP: U2.1, U2.2, U2.4
SI_STRIP1: U3.1, U3.2, U3.4
SI_STRIP2: U5.1, U5.2, U5.4
SI_STRIP3: U7.1, U7.2, U7.4
SI_STRIP4: U9.1, U9.2, U9.4
SI_STRIP5: U11.1, U11.2, U11.4
SI_STRIP6: U13.1, U13.2, U13.4
SI_STRIP7: U15.1, U15.2, U15.4
SI_STRIP8: U17.1, U17.2, U17.4
SI_STRIP9: U19.1, U19.2, U19.4
SI_STRIP10: U21.1, U21.2, U21.4
SI_STRIP11: U23.1, U23.2, U23.4
SI_STRIP12: U25.1, U25.2, U25.4
SI_STRIP13: U27.1, U27.2, U27.4
SI_STRIP14: U29.1, U29.2, U29.4
SI_STRIP15: U31.1, U31.2, U31.4
SI_STRIP16: U33.1, U33.2, U33.4
SI_STRIP17: U35.1, U35.2, U35.4
SI_STRIP18: U37.1, U37.2, U37.4
SI_STRIP19: U39.1, U39.2, U39.4
TXO: JP2.2, JP4.7, U2.23
TXO1: JP1.2, JP6.7, U3.23
TXO2: JP7.2, JP9.7, U5.23
TXO3: JP10.2, JP12.7, U7.23
TXO4: JP13.2, JP15.7, U9.23
TXO5: JP16.2, JP18.7, U11.23
TXO6: JP19.2, JP21.7, U13.23
TXO7: JP22.2, JP24.7, U15.23
TXO8: JP25.2, JP27.7, U17.23
TXO9: JP28.2, JP30.7, U19.23
TXO10: JP31.2, JP33.7, U21.23
TXO11: JP34.2, JP36.7, U23.23
TXO12: JP37.2, JP39.7, U25.23
TXO13: JP40.2, JP42.7, U27.23
TXO14: JP43.2, JP45.7, U29.23
TXO15: JP46.2, JP48.7, U31.23
TXO16: JP49.2, JP51.7, U33.23
TXO17: JP52.2, JP54.7, U35.23
TXO18: JP55.2, JP57.7, U37.23
TXO19: JP58.2, JP60.7, U39.23
VIN: C3.1, JP2.4, U1.1, U1.3
VIN1: C7.1, JP1.4, U4.1, U4.3
VIN2: C11.1, JP7.4, U6.1, U6.3
VIN3: C15.1, JP10.4, U8.1, U8.3
VIN4: C19.1, JP13.4, U10.1, U10.3
VIN5: C23.1, JP16.4, U12.1, U12.3
VIN6: C27.1, JP19.4, U14.1, U14.3
VIN7: C31.1, JP22.4, U16.1, U16.3
VIN8: C35.1, JP25.4, U18.1, U18.3
VIN9: C39.1, JP28.4, U20.1, U20.3
VIN10: C43.1, JP31.4, U22.1, U22.3
VIN11: C47.1, JP34.4, U24.1, U24.3
VIN12: C51.1, JP37.4, U26.1, U26.3
VIN13: C55.1, JP40.4, U28.1, U28.3
VIN14: C59.1, JP43.4, U30.1, U30.3
VIN15: C63.1, JP46.4, U32.1, U32.3
VIN16: C67.1, JP49.4, U34.1, U34.3
VIN17: C71.1, JP52.4, U36.1, U36.3
VIN18: C75.1, JP55.4, U38.1, U38.3
VIN19: C79.1, JP58.4, U40.1, U40.3

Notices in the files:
parts and their libraries:
RFDigital: © 2015 RF Digital Corporation
SparkFun-Aesthetics: Licensing: Creative Commons ShareAlike 4.0 International - https://creativecommons.org/licenses/by-sa/4.0
SparkFun-Aesthetics: Released under the Creative Commons Attribution Share-Alike 4.0 License
